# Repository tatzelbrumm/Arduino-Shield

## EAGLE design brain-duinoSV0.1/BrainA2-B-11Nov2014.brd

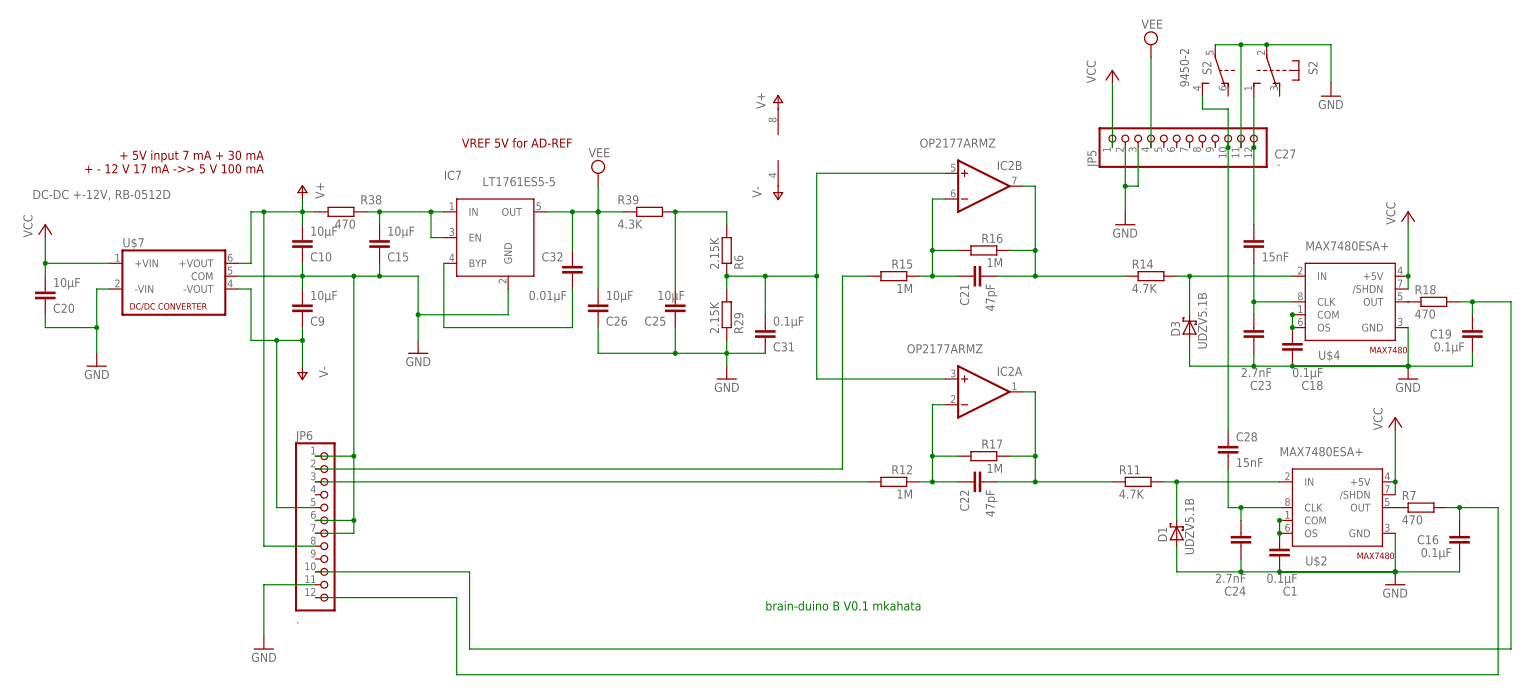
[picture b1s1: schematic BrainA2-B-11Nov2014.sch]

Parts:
C1, C16, C18, C19, C31: 0.1µF; C0603
C9, C10, C15, C20, C25, C26: 10µF; C0603
C21, C22: 47pF; C0603
C23, C24: 2.7nF; C0603
C27, C28: 15nF; C0603
C32: 0.01µF; C0603
D1, D3: UDZV5.1B; SOD323_ST
IC2: OP2177ARMZ; MSOP08
IC7: LT1761ES5-5; SOT23-5
JP5, JP6: .; 1X12
R6, R29: 2.15K; R0603
R7, R18, R38: 470; R0603
R11, R14: 4.7K; R0603
R12, R15, R16, R17: 1M; R0603
R39: 4.3K; R0603
S2: 9450-2
U$2, U$4: MAX7480ESA+; MAX7480
U$7: DC-DC +-12V, RB-0512D; RB-0515D

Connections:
GND: C1.1, C9.2, C10.1, C15.1, C16.1, C18.1, C19.1, C20.1, C23.1, C24.1, C25.1, C26.1, C31.1, D1.A, D3.A, IC7.2 (GND), JP5.2, JP5.3, JP5.11, JP6.1, JP6.6, JP6.7, JP6.11, R29.1, S2.2, S2.5, U$2.3 (GND), U$4.3 (GND), U$7.2 (-VIN), U$7.5 (COM)
unnamed: C16.2, JP6.12, R7.2
unnamed: C1.2, U$2.1 (COM), U$2.6 (OS)
unnamed: C19.2, JP6.10, R18.2
unnamed: D3.C, R14.2, U$4.2 (IN)
unnamed: R7.1, U$2.5 (OUT)
unnamed: D1.C, R11.2, U$2.2 (IN)
unnamed: C24.2, C28.2, U$2.8 (CLK)
unnamed: C22.1, IC2.2 (-IN), R12.1, R17.2
unnamed: JP6.2, R15.2
unnamed: JP6.3, R12.2
unnamed: C22.2, IC2.1 (OUT), R11.1, R17.1
unnamed: C21.1, IC2.6 (-IN), R15.1, R16.2
unnamed: C21.2, IC2.7 (OUT), R14.1, R16.1
unnamed: C27.1, JP5.12, S2.1 (S)
unnamed: C28.1, JP5.10, S2.4 (S)
unnamed: C18.2, U$4.1 (COM), U$4.6 (OS)
unnamed: R18.1, U$4.5 (OUT)
unnamed: C15.2, IC7.1 (IN), IC7.3 (EN), R38.2
unnamed: C25.2, R6.2, R39.2
unnamed: C32.1, IC7.4 (BYP)
unnamed: C31.2, IC2.3 (+IN), IC2.5 (+IN), R6.1, R29.2
unnamed: C23.2, C27.2, U$4.8 (CLK)
V+: C10.2, IC2.8 (V+), JP6.8, R38.1, U$7.6 (+VOUT)
V-: C9.1, IC2.4 (V-), JP6.5, U$7.4 (-VOUT)
VCC: C20.2, JP5.1, U$2.4 (+5V), U$2.7 (/SHDN), U$4.4 (+5V), U$4.7 (/SHDN), U$7.1 (+VIN)
VEE: C26.2, C32.2, IC7.5 (OUT), JP5.4, R39.1

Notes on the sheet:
+ 5V input 7 mA + 30 mA + - 12 V 17 mA ->> 5 V 100 mA
VREF 5V for AD-REF
brain-duino B V0.1 mkahata

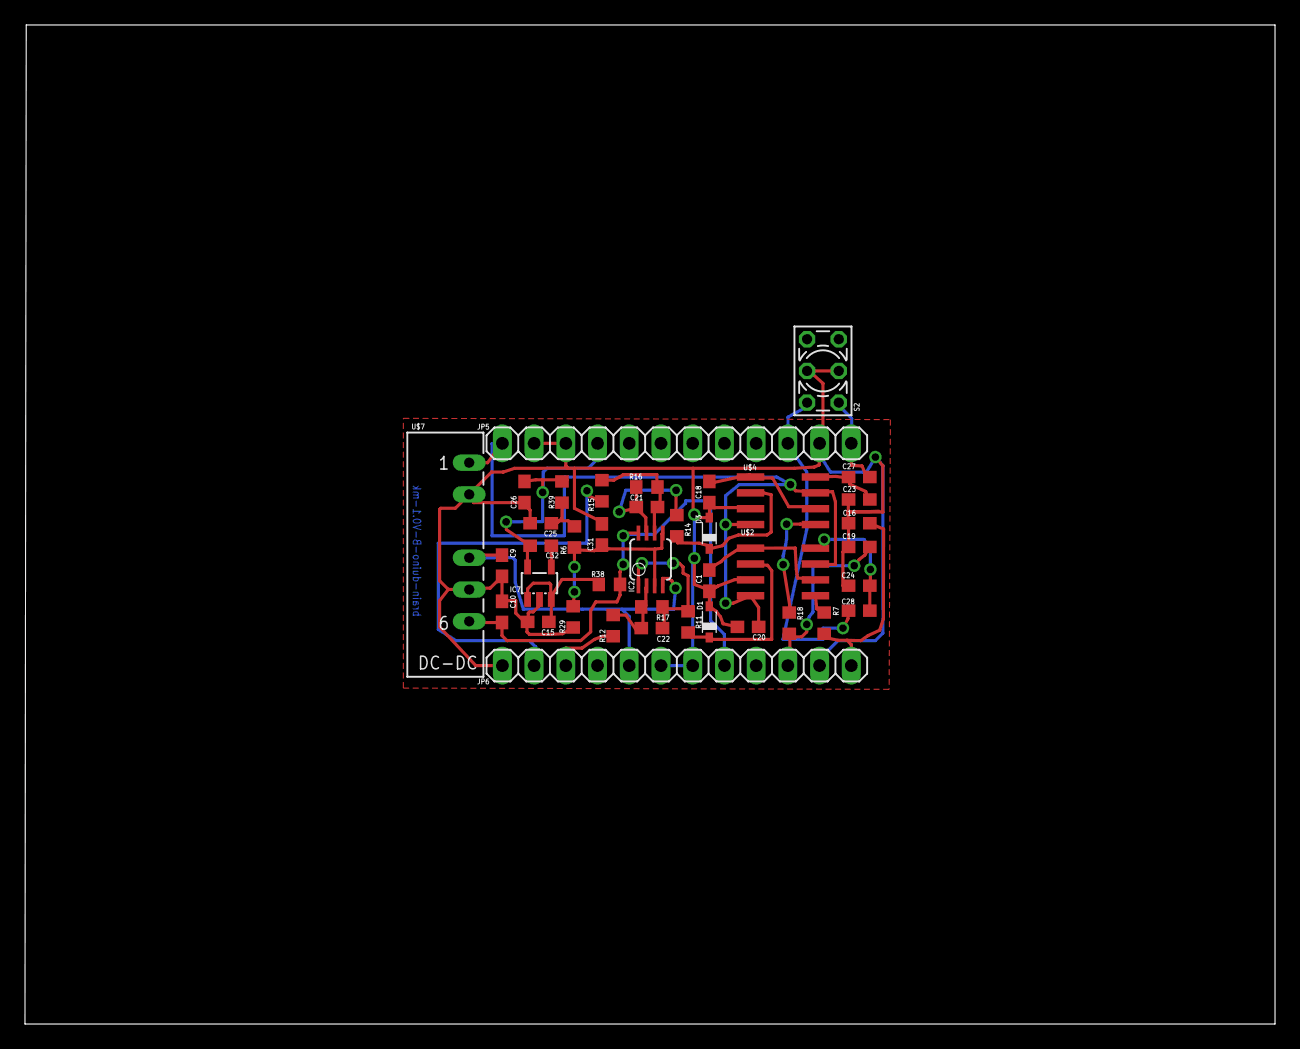
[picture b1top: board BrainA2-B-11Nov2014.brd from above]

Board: 2 copper layers, 100.1 x 80.0 mm, 40 parts (0 on the bottom side), 27 nets.

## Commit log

2015-12-26 copied .gitignore and added Eagle temporary files
2015-12-26 created clean slate eagle.epf files for projects
2015-12-26 added values to devices where ERC requires it.
2015-12-26 get rid of parameters AutoGrid, Efforts, TopRouterVariant May be caused by older version of Eagle; may not be advisable to merge.
2015-12-26 update brain-duinoV0.3/eagle.epf for my Linux version of Eagle
2015-12-26 BrainA2-B: Getting rid of some schematic level ERC errors and warnings
2015-12-28 BrainA2-A: Getting rid of some schematic level ERC errors and warnings Renamed U$1 to IC8
2015-12-28 Rename U$2->IC10 U$4->IC11 U$7->IC12
2015-12-28 Convert BrainA2-A-11Nov2014.brd to KiCAD using https://github.com/DanChianucci/Eagle2Kicad
2015-12-28 Convert BrainA2-B-11Nov2014.brd to KiCAD using https://github.com/DanChianucci/Eagle2Kicad
2015-12-28 capture brain-duinoSV0.1/eagle.epf (specific to my Linux)
2015-12-28 PoC: produce Gerber and drill files from BrainA2-A-11Nov2014KiCad.brd No settings changed from my pcbnew defaults
2015-12-28 BrainA2-A-11Nov2014KiCad.brd after running pcbnew, and saving
    after exporting Gerber and drill files
2015-12-28 PoC: produce Gerber and drill files from BrainA2-B-11Nov2014KiCad.brd No settings changed from my pcbnew defaults
2015-12-28 BrainA2-B-11Nov2014KiCad.brd after running pcbnew, and saving
    after exporting Gerber and drill files
2015-12-28 screenshots of non-default postscript export settings
2015-12-28 PoC: produce postscript files from BrainA2-A-11Nov2014KiCad.brd Settings changed from my pcbnew defaults, see screenshots.
2015-12-28 BrainA2-A-11Nov2014KiCad.brd after running pcbnew, and saving
    after exporting postscript layer files
2015-12-28 screenshots for Gerber/DXF output settings (used previously)
2015-12-28 PoC: produce postscript files from BrainA2-B-11Nov2014KiCad.brd Settings changed from my pcbnew defaults, see screenshots.
2015-12-28 BrainA2-B-11Nov2014KiCad.brd after running pcbnew, and saving after exporting postscript layer files
2015-12-29 Eagle CAM outputs for BrainA2-A, using gerb274x-4layer.cam
2015-12-29 Eagle CAM outputs for BrainA2-A, using excellon.cam
2015-12-29 Eagle CAM outputs for BrainA2-B, using gerb274x-4layer.cam
2015-12-29 Eagle CAM outputs for BrainA2-B, using excellon.cam
2015-12-29 brain-duinoSV0.1/eagle.epf update
2015-12-29 move Eagle CAM files to Eagle_export directory
